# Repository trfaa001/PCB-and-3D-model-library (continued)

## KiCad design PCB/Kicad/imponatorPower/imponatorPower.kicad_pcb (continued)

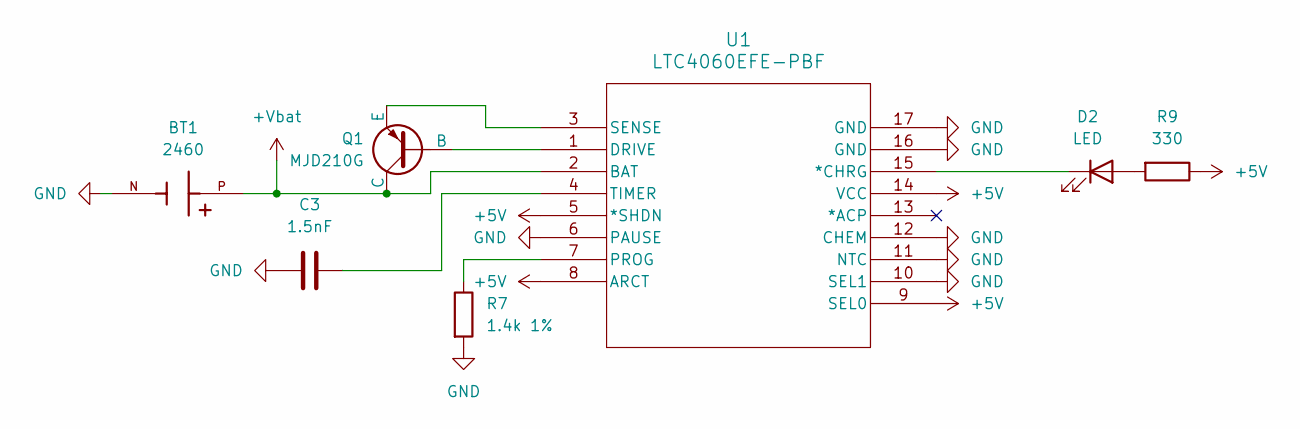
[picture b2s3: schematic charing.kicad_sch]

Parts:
BT1: 2460; BAT_2460; PARTREV B
C3: 1.5nF; C_0805_2012Metric_Pad1.18x1.45mm_HandSolder
D2: LED; LED_0805_2012Metric_Pad1.15x1.40mm_HandSolder
Q1: MJD210G; TO-252-2
R7: 1.4k 1%; R_0805_2012Metric_Pad1.20x1.40mm_HandSolder
R9: 330; R_0805_2012Metric_Pad1.20x1.40mm_HandSolder
U1: LTC4060EFE-PBF; SSOP-16_FE_LIT-L

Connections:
+Vbat: BT1.P, Q1.1 (C), U1.2 (BAT); also elsewhere on the board
GND: BT1.N, C3.1, R7.2, U1.6 (PAUSE), U1.10 (SEL1), U1.11 (NTC), U1.12 (CHEM), U1.16 (GND), U1.17 (GND); also elsewhere on the board
unnamed: D2.2 (A), R9.2
unnamed: D2.1 (K), U1.15 (*CHRG)
unnamed: Q1.2 (B), U1.1 (DRIVE)
unnamed: Q1.3 (E), U1.3 (SENSE)
unnamed: R7.1, U1.7 (PROG)
unnamed: C3.2, U1.4 (TIMER)
vdc_out: R9.1, U1.5 (*SHDN), U1.8 (ARCT), U1.9 (SEL0), U1.14 (VCC); also elsewhere on the board

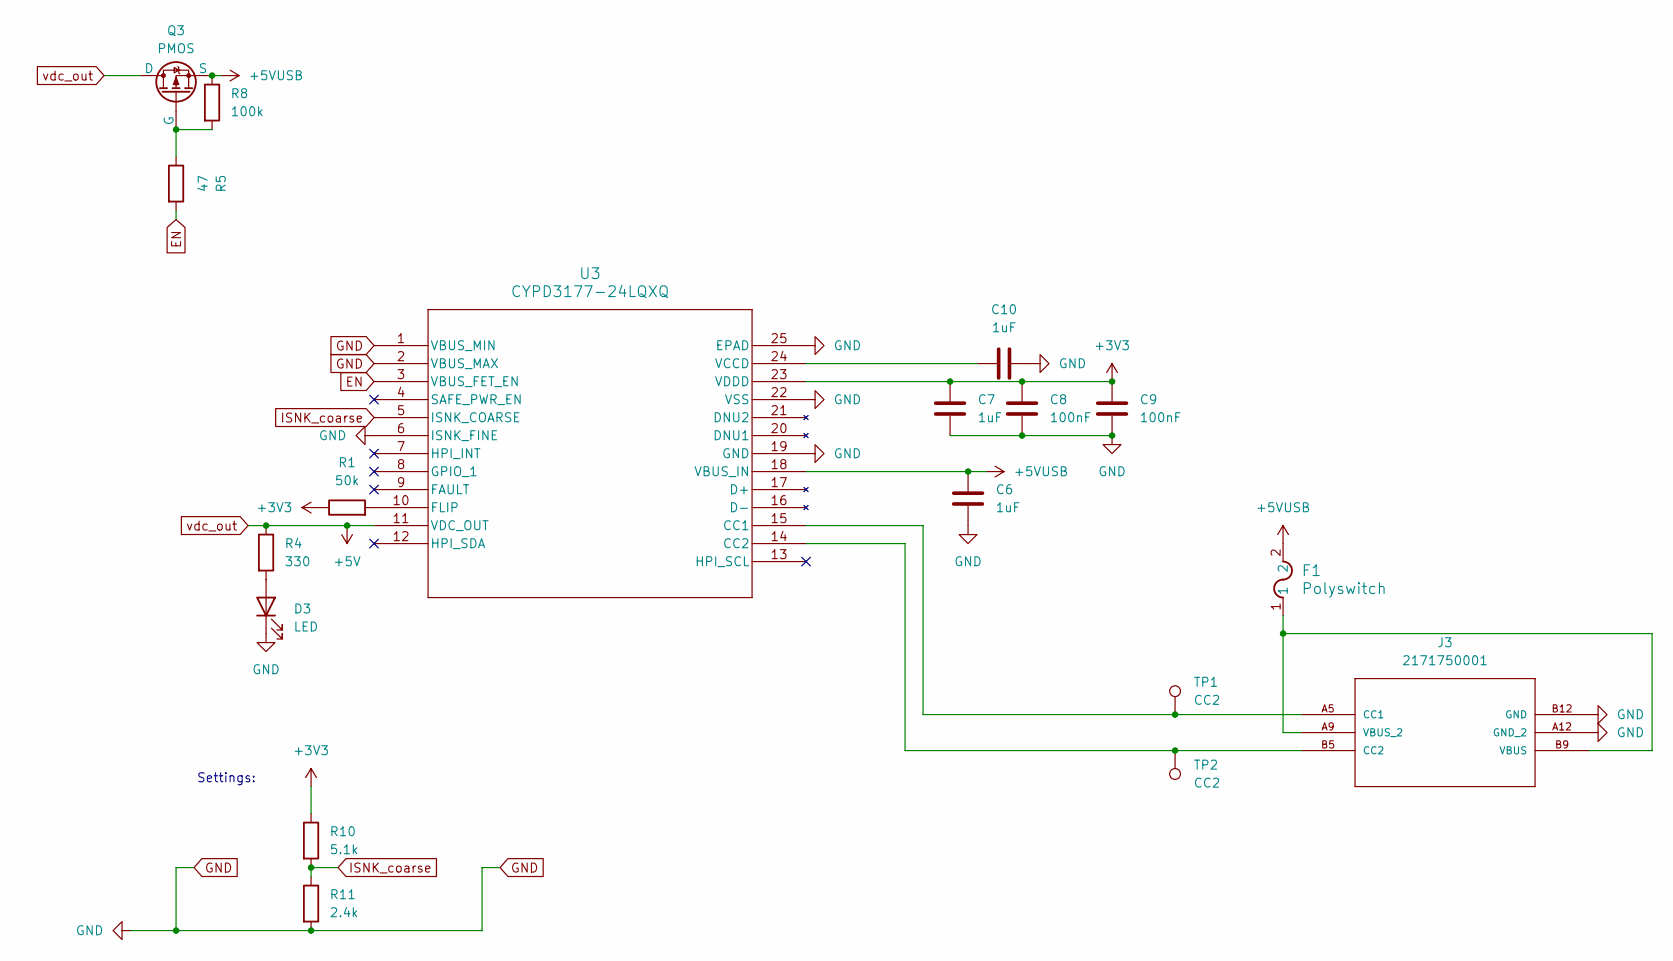
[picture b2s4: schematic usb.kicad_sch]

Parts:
C6, C7, C10: 1uF; C_0805_2012Metric_Pad1.18x1.45mm_HandSolder
C8, C9: 100nF; C_0805_2012Metric_Pad1.18x1.45mm_HandSolder
D3: LED; LED_0805_2012Metric_Pad1.15x1.40mm_HandSolder
F1: Polyswitch; Fuse_1206_3216Metric_Pad1.42x1.75mm_HandSolder
J3: 2171750001; 2171750001_MOL; MANUFACTURER_PART_NUMBER 2171750001
Q3: PMOS; SOT-23_Handsoldering
R1: 50k; R_0402_1005Metric_Pad0.72x0.64mm_HandSolder
R4: 330; R_0805_2012Metric_Pad1.20x1.40mm_HandSolder
R5: 47; R_0805_2012Metric_Pad1.20x1.40mm_HandSolder
R8: 100k; R_0805_2012Metric_Pad1.20x1.40mm_HandSolder
R10: 5.1k; R_0805_2012Metric_Pad1.20x1.40mm_HandSolder
R11: 2.4k; R_0805_2012Metric_Pad1.20x1.40mm_HandSolder
TP1, TP2: CC2; TestPoint_Pad_2.0x2.0mm
U3: CYPD3177-24LQXQ; QFN24_CYPD3177_INF-L

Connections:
+3V3: C7.2, C8.1, C9.1, R1.1, R10.1, U3.23 (VDDD)
+5VUSB: C6.2, F1.2, Q3.3 (S), R8.1, U3.18 (VBUS_IN)
EN: R5.2, U3.3 (VBUS_FET_EN)
GND: C6.1, C7.1, C8.2, C9.2, C10.2, D3.1 (K), J3.A12 (GND_2), J3.B12 (GND), R11.2, U3.1 (VBUS_MIN), U3.2 (VBUS_MAX), U3.6 (ISNK_FINE), U3.19 (GND), U3.22 (VSS), U3.25 (EPAD); also elsewhere on the board
ISNK_coarse: R10.2, R11.1, U3.5 (ISNK_COARSE)
unnamed: D3.2 (A), R4.2
unnamed: J3.A5 (CC1), TP1.1, U3.15 (CC1)
unnamed: J3.B5 (CC2), TP2.1, U3.14 (CC2)
unnamed: F1.1, J3.A9 (VBUS_2), J3.B9 (VBUS)
unnamed: Q3.2 (G), R5.1, R8.2
unnamed: R1.2, U3.10 (FLIP)
unnamed: C10.1, U3.24 (VCCD)
vdc_out: Q3.1 (D), R4.1, U3.11 (VDC_OUT); also elsewhere on the board

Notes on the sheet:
Settings:

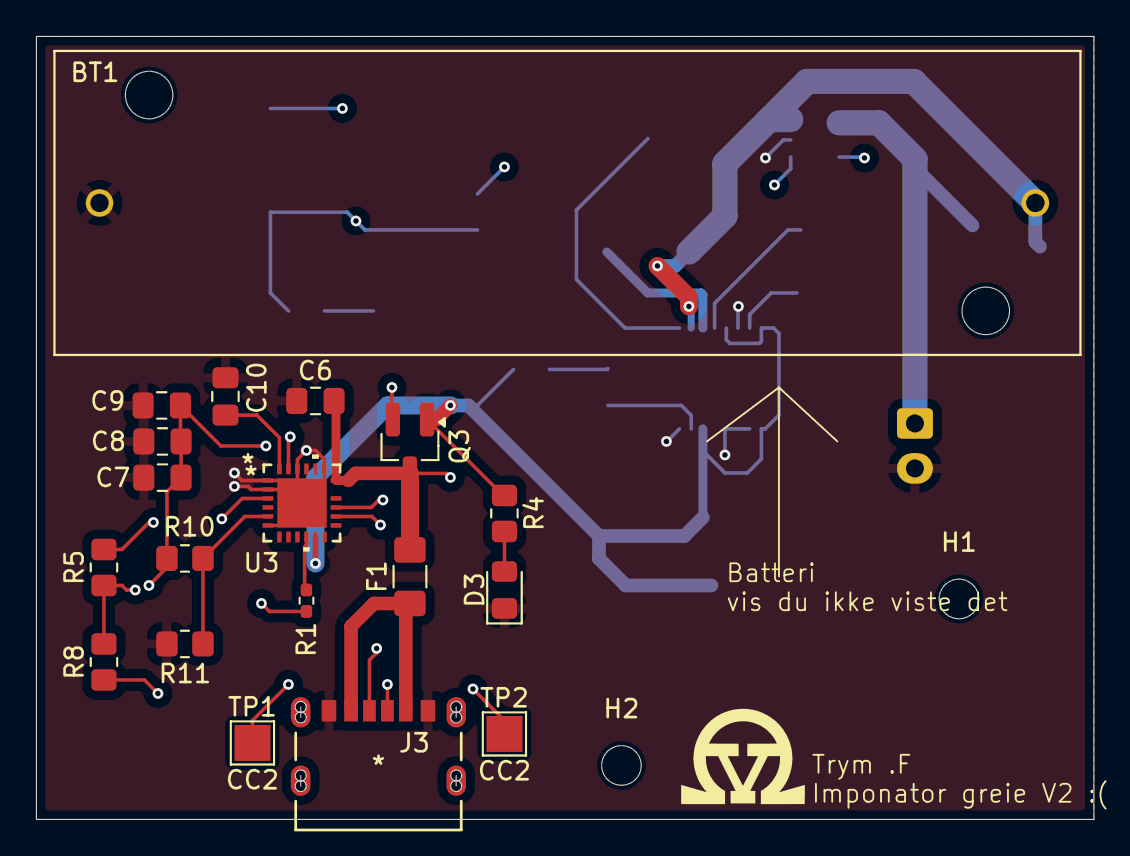
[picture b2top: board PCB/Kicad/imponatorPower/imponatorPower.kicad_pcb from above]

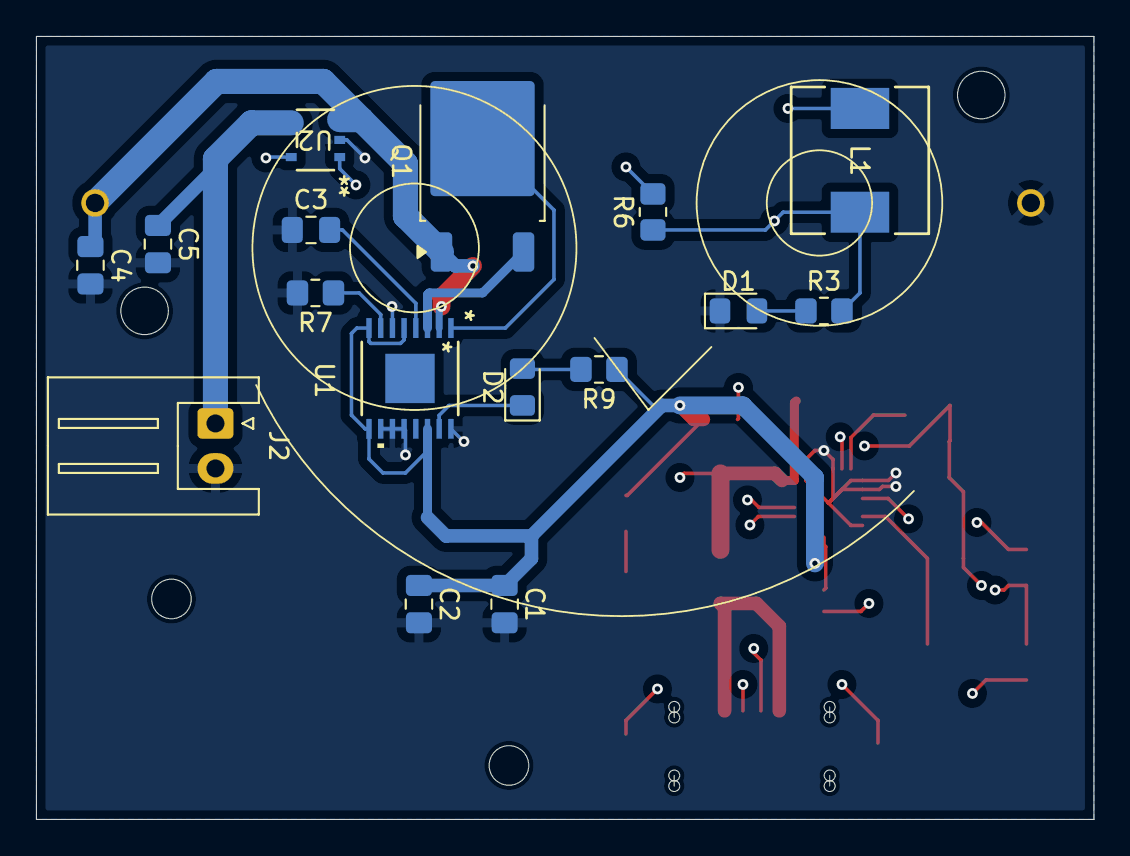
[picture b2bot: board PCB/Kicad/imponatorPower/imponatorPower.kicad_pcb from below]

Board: 4 copper layers, 58.8 x 43.5 mm, 37 parts (16 on the bottom side), 24 nets.

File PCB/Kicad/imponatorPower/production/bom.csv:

Designator,Footprint,Quantity,Value,LCSC Part #
BT1,BAT_2460,1,2460,
"C1, C2, C4, C5",0805,4,10uF,
"C10, C6, C7",0805,3,1uF,
C3,0805,1,1.5nF,
"C8, C9",0805,2,100nF,
"D1, D2, D3",0805,3,LED,
F1,1206,1,Polyswitch,
J2,JST_XH_S2B-XH-A_1x02_P2.50mm_Horizontal,1,Conn_01x02,
J3,2171750001_MOL,1,USB-C,
L1,IND_PCC-M0754M_PAN-L,1,4.7uH,
Q1,TO-252-2,1,MJD210G,
Q3,SOT-23_Handsoldering,1,PMOS,
R1,0402,1,50k,
R10,0805,1,5.1k,
R11,0805,1,2.4k,
"R3, R4, R9",0805,3,330,
R5,0805,1,47,
R6,0805,1,10K,
R7,0805,1,1.4k 1%,
R8,0805,1,100k,
"TP1, TP2",TestPoint_Pad_2.0x2.0mm,2,CC2,
U1,SSOP-16_FE_LIT-L,1,LTC4060EFE-PBF,
U2,SOT25_XC9141_TOR-L,1,XC9141B50CMR-G,
U3,QFN24_CYPD3177_INF-L,1,CYPD,

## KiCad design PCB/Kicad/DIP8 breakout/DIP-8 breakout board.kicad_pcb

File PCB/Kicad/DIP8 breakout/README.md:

# DIP8 breakout board

<!-- Project description -->
A small breakout board for any DIP8 IC.
Designed to make it easier to prototype with DIP8 IC by converting it to TH.

## images
### Schematic

### PCB design

### PCB render

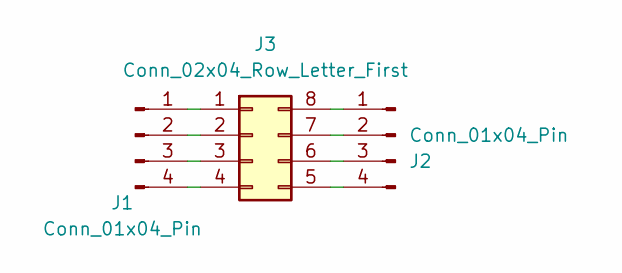
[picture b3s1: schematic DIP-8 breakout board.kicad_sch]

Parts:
J1, J2: Conn_01x04_Pin; PinHeader_1x04_P2.54mm_Vertical
J3: Conn_02x04_Row_Letter_First; OPTO_HCNR200-500E

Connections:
unnamed: J1.1, J3.1 (Pin_a1)
unnamed: J1.2, J3.2 (Pin_a2)
unnamed: J1.3, J3.3 (Pin_a3)
unnamed: J1.4, J3.4 (Pin_a4)
unnamed: J2.1, J3.8 (Pin_b1)
unnamed: J2.2, J3.7 (6Pin_b2)
unnamed: J2.3, J3.6 (Pin_b3)
unnamed: J2.4, J3.5 (Pin_b4)

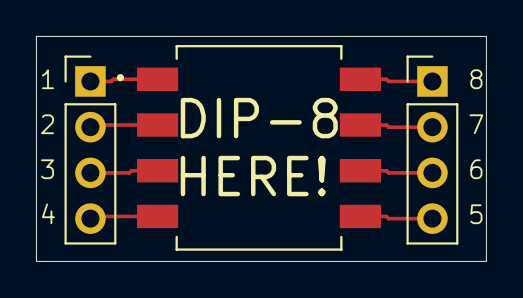
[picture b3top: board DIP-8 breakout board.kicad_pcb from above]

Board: 2 copper layers, 25.0 x 12.5 mm, 3 parts (0 on the bottom side), 8 nets.

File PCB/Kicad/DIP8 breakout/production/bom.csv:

Designator,Footprint,Quantity,Value,LCSC Part #
"J1, J2",PinHeader_1x04_P2.54mm_Vertical,2,Conn_01x04_Pin,
J3,OPTO_HCNR200-500E,1,Conn_02x04_Row_Letter_First,

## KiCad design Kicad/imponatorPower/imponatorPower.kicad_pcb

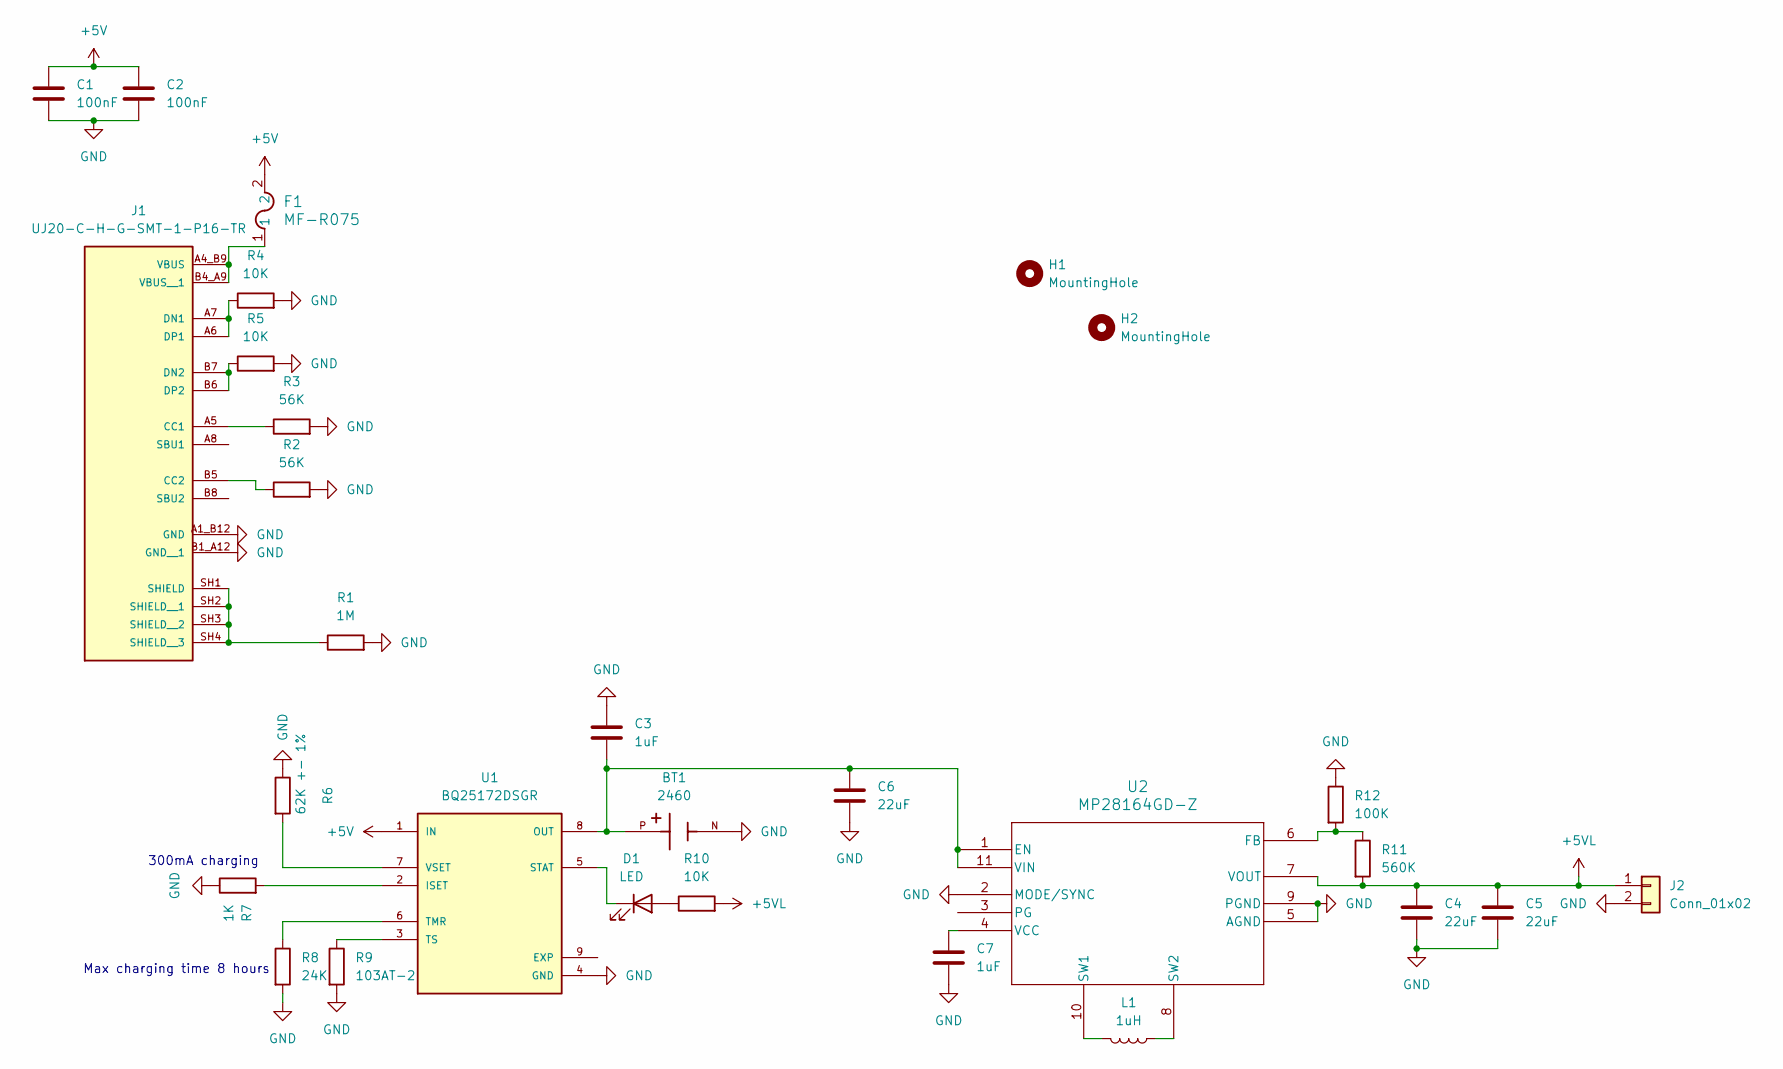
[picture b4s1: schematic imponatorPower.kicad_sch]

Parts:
BT1: 2460; BAT_2460; PARTREV B
C1, C2: 100nF; C_0805_2012Metric_Pad1.18x1.45mm_HandSolder
C3, C7: 1uF; C_0805_2012Metric_Pad1.18x1.45mm_HandSolder
C4, C5, C6: 22uF; C_0805_2012Metric_Pad1.18x1.45mm_HandSolder
D1: LED; LED_0201_0603Metric_Pad0.64x0.40mm_HandSolder
F1: MF-R075; FUS_MF-R075_BRN
H1, H2: MountingHole; MountingHole_2.2mm_M2
J1: UJ20-C-H-G-SMT-1-P16-TR; SAMESKY_UJ20-C-H-G-SMT-1-P16-TR; PARTREV 1.0
J2: Conn_01x02; JST_XH_S2B-XH-A_1x02_P2.50mm_Horizontal
L1: 1uH; R_Bare_Metal_Element_L21.3mm_W4.8mm_P20.30mm
R1: 1M; R_1206_3216Metric_Pad1.30x1.75mm_HandSolder
R2, R3: 56K; R_1206_3216Metric_Pad1.30x1.75mm_HandSolder
R4, R5, R10: 10K; R_1206_3216Metric_Pad1.30x1.75mm_HandSolder
R6: 62K +- 1%; R_0603_1608Metric_Pad0.98x0.95mm_HandSolder
R7: 1K; R_1206_3216Metric_Pad1.30x1.75mm_HandSolder
R8: 24K; R_1206_3216Metric_Pad1.30x1.75mm_HandSolder
R9: 103AT-2; R_Bare_Metal_Element_L21.3mm_W4.8mm_P20.30mm
R11: 560K; R_1206_3216Metric_Pad1.30x1.75mm_HandSolder
R12: 100K; R_1206_3216Metric_Pad1.30x1.75mm_HandSolder
U1: BQ25172DSGR; IC_BQ25172DSGR; PARTREV June 2022
U2: MP28164GD-Z; QFN-11_MP28164_MNP

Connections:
+5V: C1.1, C2.1, F1.2, U1.1 (IN)
+5VL: C4.1, C5.1, J2.1, R10.2, R11.2, U2.7 (VOUT)
GND: BT1.N, C1.2, C2.2, C3.1, C4.2, C5.2, C6.2, C7.2, J1.A1_B12 (GND), J1.B1_A12 (GND__1), J2.2, R1.2, R2.2, R3.2, R4.2, R5.2, R6.1, R7.1, R8.2, R9.2, R12.1, U1.4 (GND), U2.2 (MODE/SYNC), U2.5 (AGND), U2.9 (PGND)
unnamed: D1.2 (A), R10.1
unnamed: D1.1 (K), U1.5 (STAT)
unnamed: J1.A5 (CC1), R3.1
unnamed: J1.B5 (CC2), R2.1
unnamed: J1.A6 (DP1), J1.A7 (DN1), R4.1
unnamed: J1.B6 (DP2), J1.B7 (DN2), R5.1
unnamed: J1.SH1 (SHIELD), J1.SH2 (SHIELD__1), J1.SH3 (SHIELD__2), J1.SH4 (SHIELD__3), R1.1
unnamed: F1.1, J1.A4_B9 (VBUS), J1.B4_A9 (VBUS__1)
unnamed: R7.2, U1.2 (ISET)
unnamed: BT1.P, C3.2, C6.1, U1.8 (OUT), U2.1 (EN), U2.11 (VIN)
unnamed: R8.1, U1.6 (TMR)
unnamed: R9.1, U1.3 (TS)
unnamed: R6.2, U1.7 (VSET)
unnamed: R11.1, R12.2, U2.6 (FB)
unnamed: L1.2, U2.10 (SW1)
unnamed: L1.1, U2.8 (SW2)
unnamed: C7.1, U2.4 (VCC)

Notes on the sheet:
300mA charging
Max charging time 8 hours

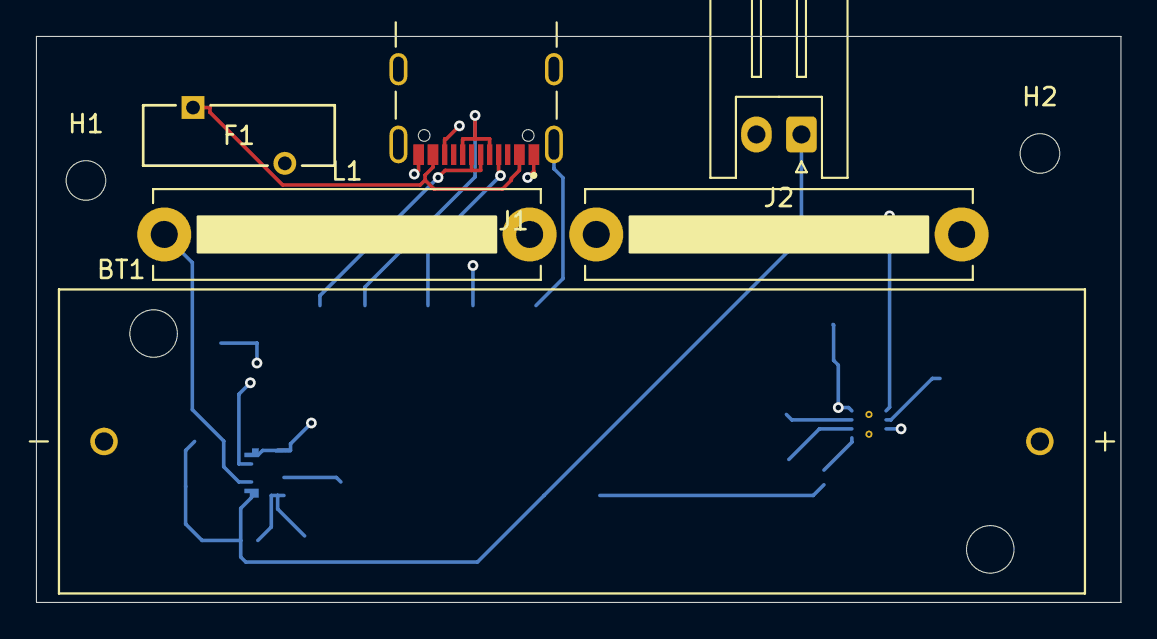
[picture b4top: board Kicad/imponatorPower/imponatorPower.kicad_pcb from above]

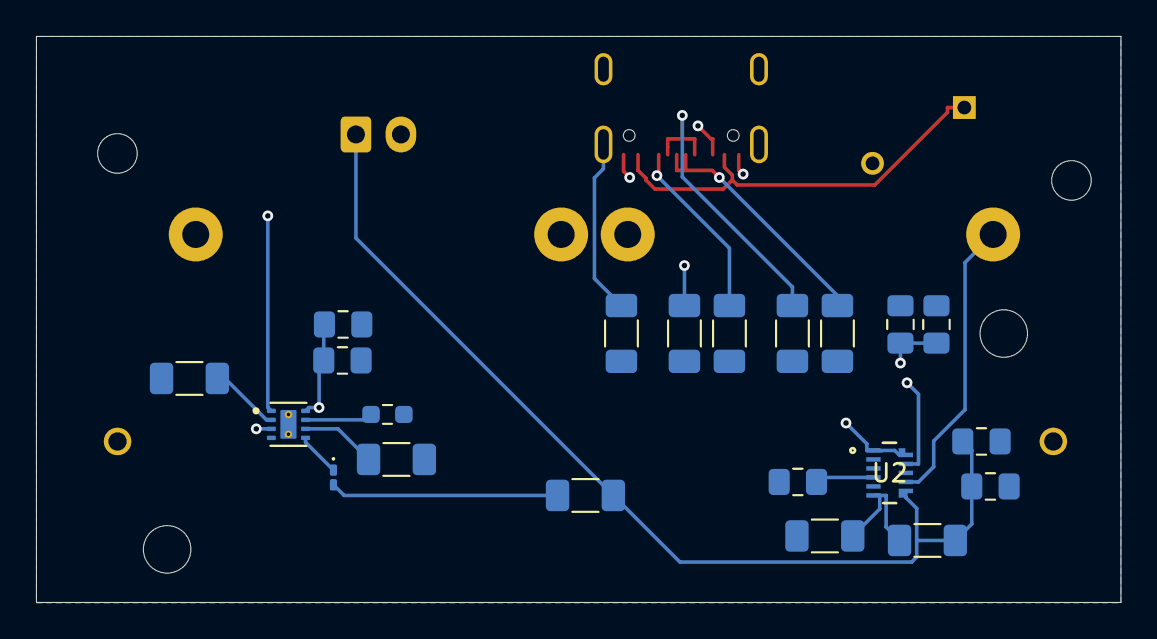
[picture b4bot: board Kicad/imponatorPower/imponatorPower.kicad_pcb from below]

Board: 4 copper layers, 60.2 x 31.4 mm, 29 parts (21 on the bottom side), 20 nets.

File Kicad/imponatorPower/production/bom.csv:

Designator,Footprint,Quantity,Value,LCSC Part #
BT1,BAT_2460,1,2460,
"C1, C2",0805,2,100nF,
"C3, C7",0805,2,1uF,
"C4, C5, C6",0805,3,22uF,
D1,0201,1,LED,
F1,FUS_MF-R075_BRN,1,MF-R075,
J1,SAMESKY_UJ20-C-H-G-SMT-1-P16-TR,1,UJ20-C-H-G-SMT-1-P16-TR,
J2,JST_XH_S2B-XH-A_1x02_P2.50mm_Horizontal,1,Conn_01x02,
L1,R_Bare_Metal_Element_L21.3mm_W4.8mm_P20.30mm,1,1uH,
R1,1206,1,1M,
"R10, R4, R5",1206,3,10K,
R11,1206,1,560K,
R12,1206,1,100K,
"R2, R3",1206,2,56K,
R6,0603,1,62K +- 1%,
R7,1206,1,1K,
R8,1206,1,24K,
R9,R_Bare_Metal_Element_L21.3mm_W4.8mm_P20.30mm,1,103AT-2,
U1,IC_BQ25172DSGR,1,BQ25172DSGR,
U2,QFN-11_MP28164_MNP,1,MP28164GD-Z,

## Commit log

2025-10-03 HCNR200 breakout / DIP8 breakout
2025-10-03 Added a bunch of components and made a battery circuit for the OV imponator
2026-01-25 Cleaning up before publishing to public.
    Added a general structure to the library.
2026-01-25 Fixed wrong use of / and \
2026-01-25 Added my sim racing table clamp to the library.
2026-01-25 Created a example markdown.
2026-01-25 Fixed writing error
    The motor table clamp is not untested.
2026-01-25 Fixed readme and folder structured.
    Wrong link to project in readme.
    Renamed folders to not contain spaces.
2026-01-25 Rename render.PNG to render.png
2026-03-15 Added Screen mount and shaft attachment
2026-03-15 Fixed bug in readme that lead to the text being on the left of an image
2026-03-15 Previous commit sadly didn't fix the bug, it only fixed it in my markdown viewer : (
2026-04-04 Finished the second iteration of the imponatorPower project
2026-04-04 Updated readmes
2026-04-12 Initial upload of imponatorPower v2. Schematic finished
2026-04-13 PCB routed, not ready for production
2026-05-25 Finish 4 layer PCB, starting with v2.1 with 6 layers.
2026-05-25 Removed components to make new layout on 6 layer board
2026-05-25 Added components to PCB on V2.1
2026-05-26 6 layer version of imponatorPower routed.
2026-05-29 Fixed corrupted readmes, added some drawing to ImponatorPower V2.1 Silkscreen and made an readme for ImponatorPower V2.1 with added images of the PCB layout.
